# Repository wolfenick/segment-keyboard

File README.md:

# SEGMENT Keyboard

SEGMENT is a 60% form factor keyboard featuring only through-hole components, drawing design inspiration from PCB's of the 1980s. This project is still in the early stages of design and testing.

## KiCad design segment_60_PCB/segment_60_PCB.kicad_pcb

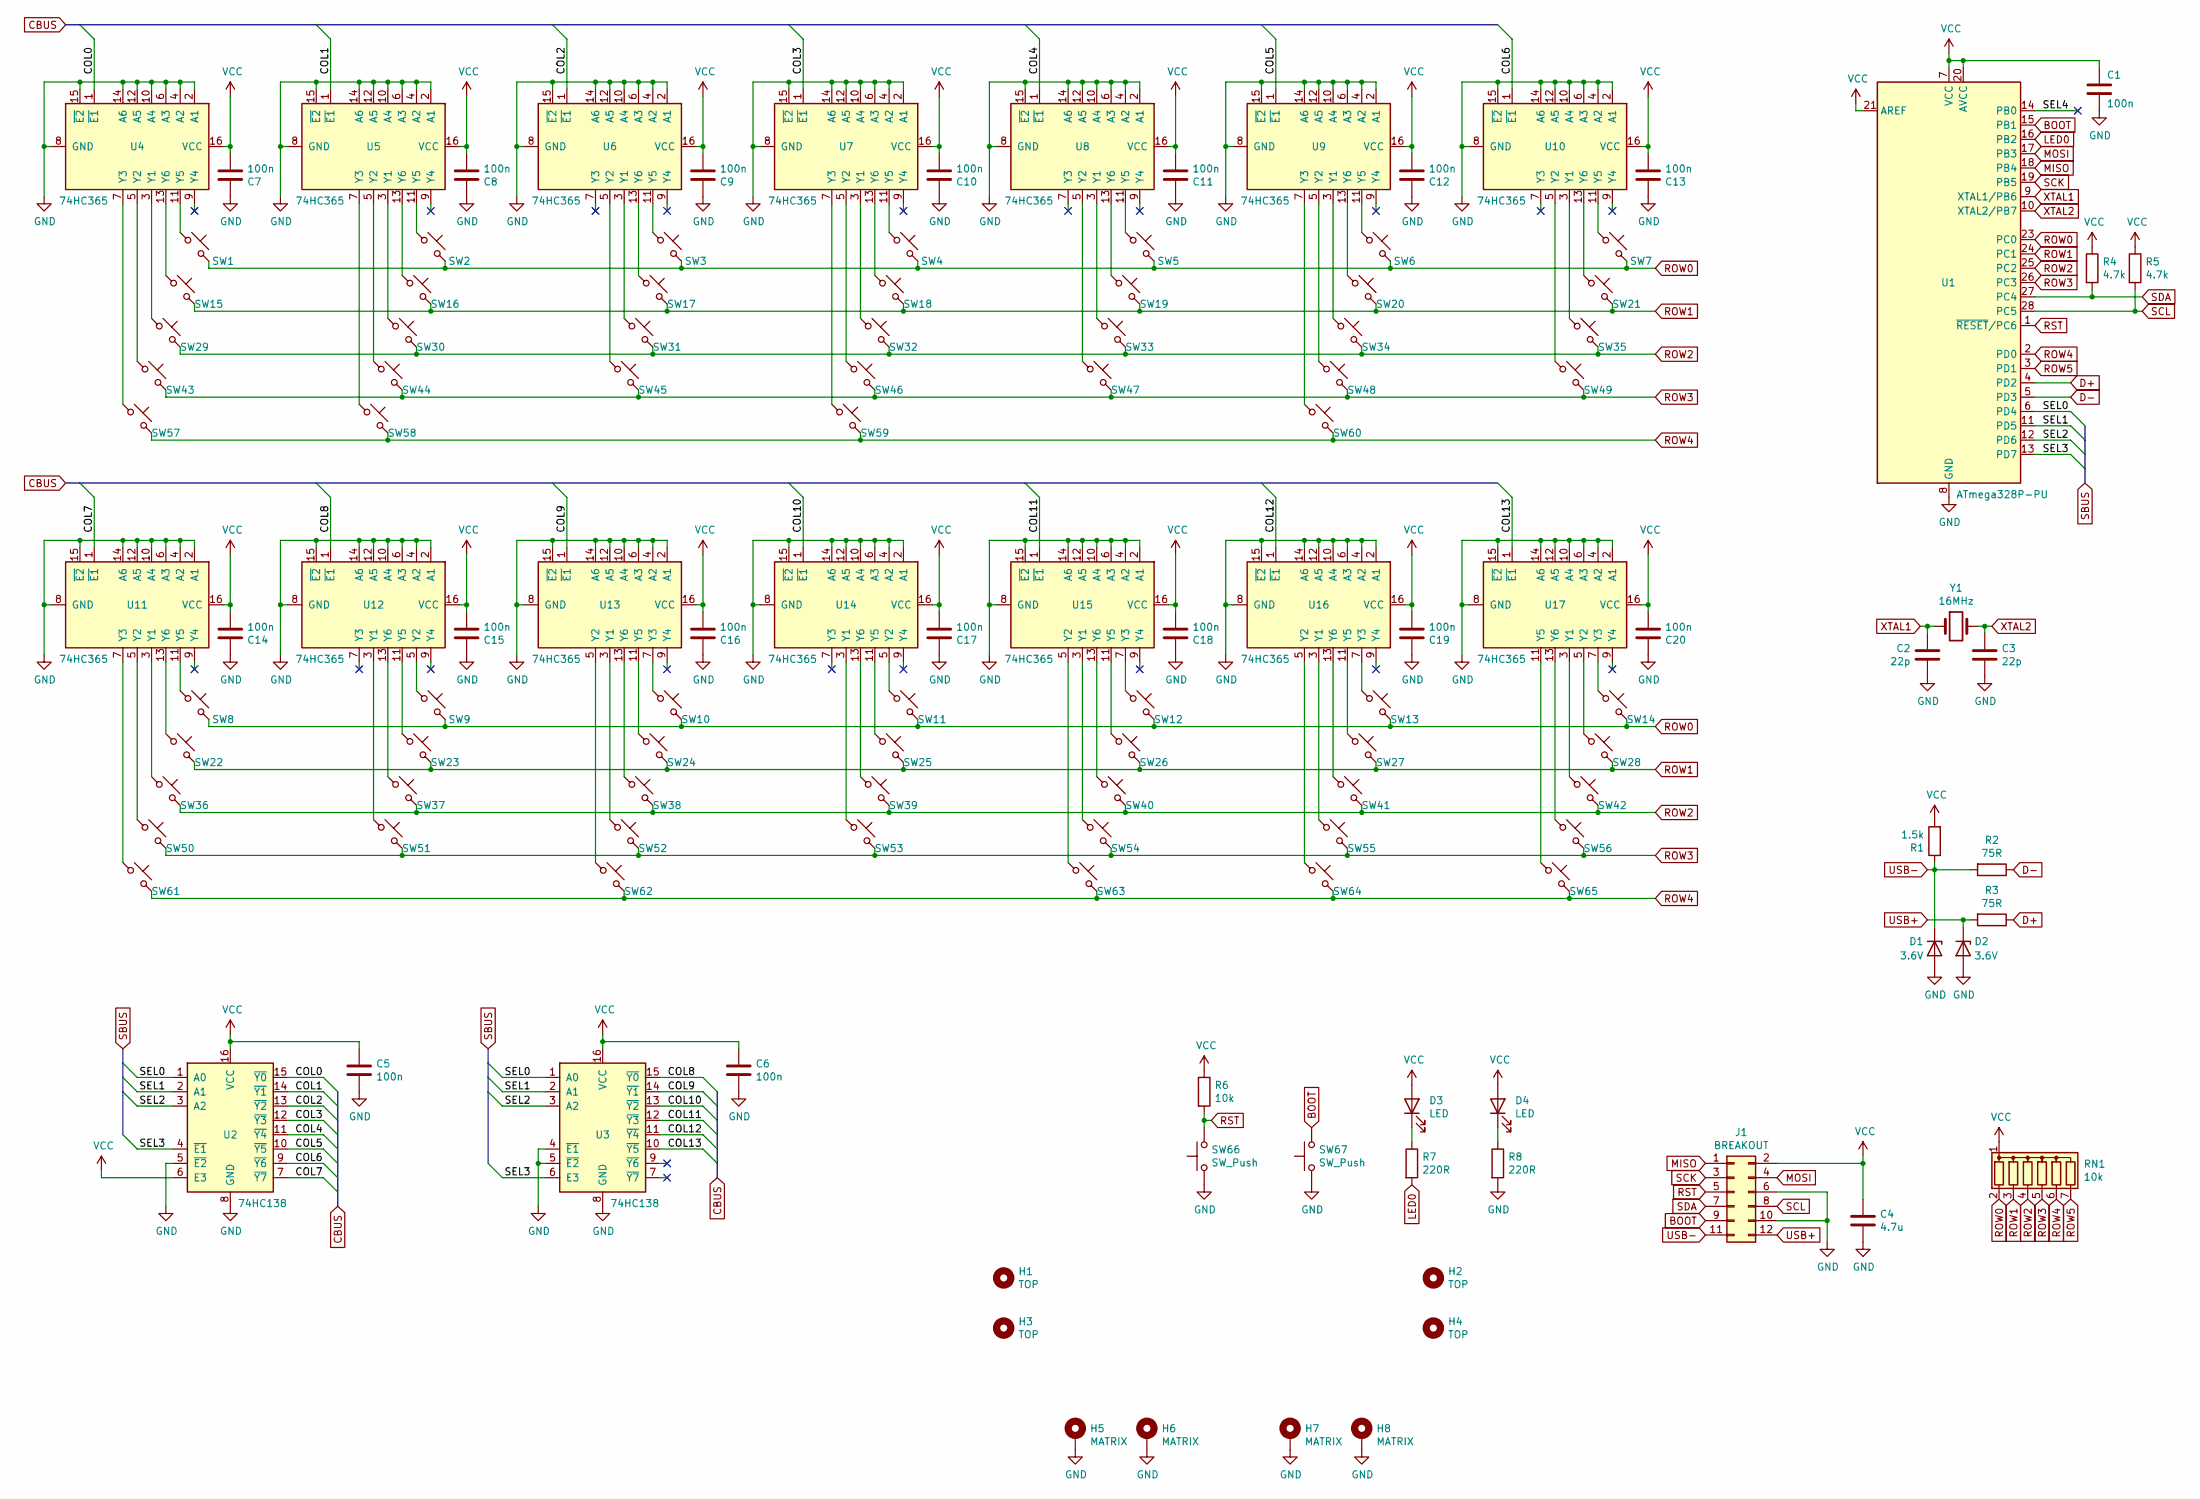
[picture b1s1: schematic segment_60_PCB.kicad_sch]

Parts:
C1: 100n; C_Axial_L3.8mm_D2.6mm_P10.16mm_Horizontal
C2, C3: 22p; C_Disc_D3.0mm_W1.6mm_P2.50mm
C4: 4.7u; CP_Axial_L11.0mm_D5.0mm_P18.00mm_Horizontal
C5, C6, C7, C8, C9, C10, C11, C12, C13, C14, C15, C16, C17, C18, C19, C20: 100n; C_Axial_L3.8mm_D2.6mm_P7.62mm_Horizontal
D1, D2: 3.6V; D_DO-35_SOD27_P10.16mm_Horizontal
D3, D4: LED; LED_D5.0mm
H1, H2, H3, H4: TOP; MountingHole_3.2mm_M3
H5, H6, H7, H8: MATRIX; MountingHole_3.2mm_M3_Pad
J1: BREAKOUT; IDC-Header_2x06_P2.54mm_Vertical
R1: 1.5k; R_Axial_DIN0207_L6.3mm_D2.5mm_P10.16mm_Horizontal
R2, R3: 75R; R_Axial_DIN0207_L6.3mm_D2.5mm_P10.16mm_Horizontal
R4, R5: 4.7k; R_Axial_DIN0207_L6.3mm_D2.5mm_P10.16mm_Horizontal
R6: 10k; R_Axial_DIN0207_L6.3mm_D2.5mm_P10.16mm_Horizontal
R7, R8: 220R; R_Axial_DIN0207_L6.3mm_D2.5mm_P10.16mm_Horizontal
RN1: 10k; R_Array_SIP7
SW1, SW2, SW3, SW4, SW5, SW6, SW7, SW8, SW9, SW10, SW11, SW12, SW13, SW16, SW17, SW18, SW19, SW20, SW21, SW22, SW23, SW24, SW25, SW26, SW27, SW28, SW30, SW31, SW32, SW33, SW34, SW35, SW36, SW37, SW38, SW39, SW40, SW44, SW45, SW46, SW47, SW48, SW49, SW50, SW51, SW52, SW53, SW54, SW56, SW58, SW64: SW_Push_45deg; Segment_MX_1.00u_PCB
SW14: SW_Push_45deg; Segment_MX_1.00u_2.00u_PCB
SW15, SW57, SW59, SW63, SW65: SW_Push_45deg; Segment_MX_1.50u_PCB
SW29: SW_Push_45deg; Segment_MX_1.25u_1.75u_PCB
SW41: SW_Push_45deg; Segment_MX_1.00u_2.25u_PCB
SW42: SW_Push_45deg; Segment_MX_1.50u_ISO_PCB
SW43: SW_Push_45deg; Segment_MX_1.25u_2.25u_PCB
SW55: SW_Push_45deg; Segment_MX_1.75u_2.75u_PCB
SW60, SW62: SW_Push_45deg; Segment_MX_2.75u_PCB
SW61: SW_Push_45deg; Segment_MX_7.00u_PCB
SW66, SW67: SW_Push; SW_PUSH_6mm
U1: ATmega328P-PU; DIP-28_W7.62mm
U2, U3: 74HC138; DIP-16_W7.62mm
U4, U5, U6, U7, U8, U9, U10, U11, U12, U13, U14, U15, U16, U17: 74HC365; DIP-16_W7.62mm
Y1: 16MHz; Crystal_HC49-4H_Vertical

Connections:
/COL0: U2.15 (~Y0), U4.1 (~E1)
/COL1: U2.14 (~Y1), U5.1 (~E1)
/COL2: U2.13 (~Y2), U6.1 (~E1)
/COL3: U2.12 (~Y3), U7.1 (~E1)
/COL4: U2.11 (~Y4), U8.1 (~E1)
/COL5: U2.10 (~Y5), U9.1 (~E1)
/COL6: U2.9 (~Y6), U10.1 (~E1)
/COL7: U2.7 (~Y7), U11.1 (~E1)
/COL8: U3.15 (~Y0), U12.1 (~E1)
/COL9: U3.14 (~Y1), U13.1 (~E1)
/COL10: U3.13 (~Y2), U14.1 (~E1)
/COL11: U3.12 (~Y3), U15.1 (~E1)
/COL12: U3.11 (~Y4), U16.1 (~E1)
/COL13: U3.10 (~Y5), U17.1 (~E1)
/SEL0: U1.6 (PD4), U2.1 (A0), U3.1 (A0)
/SEL1: U1.11 (PD5), U2.2 (A1), U3.2 (A1)
/SEL2: U1.12 (PD6), U2.3 (A2), U3.3 (A2)
/SEL3: U1.13 (PD7), U2.4 (~E1), U3.6 (E3)
/SEL4: U1.14 (PB0)
BOOT: J1.9, SW67.2, U1.15 (PB1)
D+: R3.1, U1.4 (PD2)
D-: R2.1, U1.5 (PD3)
GND: C1.2, C2.1, C3.2, C4.2, C5.2, C6.2, C7.1, C8.1, C9.1, C10.1, C11.1, C12.1, C13.1, C14.1, C15.1, C16.1, C17.1, C18.1, C19.1, C20.1, D1.2 (A), D2.2 (A), H5.1, H6.1, H7.1, H8.1, J1.6, J1.10, R8.2, SW66.1, SW67.1, U1.8 (GND), U1.22 (GND), U2.5 (~E2), U2.8 (GND), U3.4 (~E1), U3.5 (~E2), U3.8 (GND), U4.2 (A1), U4.4 (A2), U4.6 (A3), U4.8 (GND), U4.10 (A4), U4.12 (A5), U4.14 (A6), U4.15 (~E2), U5.2 (A1), U5.4 (A2), U5.6 (A3), U5.8 (GND), U5.10 (A4), U5.12 (A5), U5.14 (A6), U5.15 (~E2), U6.2 (A1), U6.4 (A2), U6.6 (A3), U6.8 (GND), U6.10 (A4), U6.12 (A5), U6.14 (A6), U6.15 (~E2), U7.2 (A1), U7.4 (A2), U7.6 (A3), U7.8 (GND), U7.10 (A4), U7.12 (A5), U7.14 (A6), U7.15 (~E2), U8.2 (A1), U8.4 (A2), U8.6 (A3), U8.8 (GND), U8.10 (A4), U8.12 (A5), U8.14 (A6), U8.15 (~E2), U9.2 (A1), U9.4 (A2), U9.6 (A3), U9.8 (GND), U9.10 (A4), U9.12 (A5), U9.14 (A6), U9.15 (~E2), U10.2 (A1), U10.4 (A2), U10.6 (A3), U10.8 (GND), U10.10 (A4), U10.12 (A5), U10.14 (A6), U10.15 (~E2), U11.2 (A1), U11.4 (A2), U11.6 (A3), U11.8 (GND), U11.10 (A4), U11.12 (A5), U11.14 (A6), U11.15 (~E2), U12.2 (A1), U12.4 (A2), U12.6 (A3), U12.8 (GND), U12.10 (A4), U12.12 (A5), U12.14 (A6), U12.15 (~E2), U13.2 (A1), U13.4 (A2), U13.6 (A3), U13.8 (GND), U13.10 (A4), U13.12 (A5), U13.14 (A6), U13.15 (~E2), U14.2 (A1), U14.4 (A2), U14.6 (A3), U14.8 (GND), U14.10 (A4), U14.12 (A5), U14.14 (A6), U14.15 (~E2), U15.2 (A1), U15.4 (A2), U15.6 (A3), U15.8 (GND), U15.10 (A4), U15.12 (A5), U15.14 (A6), U15.15 (~E2), U16.2 (A1), U16.4 (A2), U16.6 (A3), U16.8 (GND), U16.10 (A4), U16.12 (A5), U16.14 (A6), U16.15 (~E2), U17.2 (A1), U17.4 (A2), U17.6 (A3), U17.8 (GND), U17.10 (A4), U17.12 (A5), U17.14 (A6), U17.15 (~E2); also elsewhere on the board
LED0: R7.2, U1.16 (PB2)
MISO: J1.1, U1.18 (PB4)
MOSI: J1.4, U1.17 (PB3)
unnamed: D3.1 (K), R7.1
unnamed: D4.1 (K), R8.1
unnamed: SW1.1, U4.11 (Y5)
unnamed: SW2.1, U5.11 (Y5)
unnamed: SW3.1, U6.11 (Y5)
unnamed: SW4.1, U7.11 (Y5)
unnamed: SW5.1, U8.11 (Y5)
unnamed: SW6.1, U9.11 (Y5)
unnamed: SW7.1, U10.11 (Y5)
unnamed: SW8.1, U11.11 (Y5)
unnamed: SW9.1, U12.5 (Y2)
unnamed: SW10.1, U13.7 (Y3)
unnamed: SW11.1, U14.5 (Y2)
unnamed: SW12.1, U15.7 (Y3)
unnamed: SW13.1, U16.7 (Y3)
unnamed: SW14.1, U17.7 (Y3)
unnamed: SW15.1, U4.13 (Y6)
unnamed: SW16.1, U5.13 (Y6)
unnamed: SW17.1, U6.13 (Y6)
unnamed: SW18.1, U7.13 (Y6)
unnamed: SW19.1, U8.13 (Y6)
unnamed: SW20.1, U9.13 (Y6)
unnamed: SW21.1, U10.13 (Y6)
unnamed: SW22.1, U11.13 (Y6)
unnamed: SW23.1, U12.11 (Y5)
unnamed: SW24.1, U13.11 (Y5)
unnamed: SW25.1, U14.11 (Y5)
unnamed: SW26.1, U15.11 (Y5)
unnamed: SW27.1, U16.11 (Y5)
unnamed: SW28.1, U17.5 (Y2)
unnamed: SW29.1, U4.3 (Y1)
unnamed: SW30.1, U5.3 (Y1)
unnamed: SW31.1, U6.3 (Y1)
unnamed: SW32.1, U7.3 (Y1)
unnamed: SW33.1, U8.3 (Y1)
unnamed: SW34.1, U9.3 (Y1)
unnamed: SW35.1, U10.3 (Y1)
unnamed: SW36.1, U11.3 (Y1)
unnamed: SW37.1, U12.13 (Y6)
unnamed: SW38.1, U13.13 (Y6)
unnamed: SW39.1, U14.13 (Y6)
unnamed: SW40.1, U15.13 (Y6)
unnamed: SW41.1, U16.13 (Y6)
unnamed: SW42.1, U17.3 (Y1)
unnamed: SW43.1, U4.5 (Y2)
unnamed: SW44.1, U5.5 (Y2)
unnamed: SW45.1, U6.5 (Y2)
unnamed: SW46.1, U7.5 (Y2)
unnamed: SW47.1, U8.5 (Y2)
unnamed: SW48.1, U9.5 (Y2)
unnamed: SW49.1, U10.5 (Y2)
unnamed: SW50.1, U11.5 (Y2)
unnamed: SW51.1, U12.3 (Y1)
unnamed: SW52.1, U13.3 (Y1)
unnamed: SW53.1, U14.3 (Y1)
unnamed: SW54.1, U15.3 (Y1)
unnamed: SW55.1, U16.3 (Y1)
unnamed: SW56.1, U17.13 (Y6)
unnamed: SW57.1, U4.7 (Y3)
unnamed: SW58.1, U5.7 (Y3)
unnamed: SW59.1, U7.7 (Y3)
unnamed: SW60.1, U9.7 (Y3)
unnamed: SW61.1, U11.7 (Y3)
unnamed: SW62.1, U13.5 (Y2)
unnamed: SW63.1, U15.5 (Y2)
unnamed: SW64.1, U16.5 (Y2)
unnamed: SW65.1, U17.11 (Y5)
ROW0: RN1.2 (R1), SW1.2, SW2.2, SW3.2, SW4.2, SW5.2, SW6.2, SW7.2, SW8.2, SW9.2, SW10.2, SW11.2, SW12.2, SW13.2, SW14.2, U1.23 (PC0)
ROW1: RN1.3 (R2), SW15.2, SW16.2, SW17.2, SW18.2, SW19.2, SW20.2, SW21.2, SW22.2, SW23.2, SW24.2, SW25.2, SW26.2, SW27.2, SW28.2, U1.24 (PC1)
ROW2: RN1.4 (R3), SW29.2, SW30.2, SW31.2, SW32.2, SW33.2, SW34.2, SW35.2, SW36.2, SW37.2, SW38.2, SW39.2, SW40.2, SW41.2, SW42.2, U1.25 (PC2)
ROW3: RN1.5 (R4), SW43.2, SW44.2, SW45.2, SW46.2, SW47.2, SW48.2, SW49.2, SW50.2, SW51.2, SW52.2, SW53.2, SW54.2, SW55.2, SW56.2, U1.26 (PC3)
ROW4: RN1.6 (R5), SW57.2, SW58.2, SW59.2, SW60.2, SW61.2, SW62.2, SW63.2, SW64.2, SW65.2, U1.2 (PD0)
ROW5: RN1.7 (R6), U1.3 (PD1)
RST: J1.5, R6.2, SW66.2, U1.1 (~RESET/PC6)
SCK: J1.3, U1.19 (PB5)
SCL: J1.8, R5.2, U1.28 (PC5)
SDA: J1.7, R4.2, U1.27 (PC4)
USB+: D2.1 (K), J1.12, R3.2
USB-: D1.1 (K), J1.11, R1.1, R2.2
VCC: C1.1, C4.1, C5.1, C6.1, C7.2, C8.2, C9.2, C10.2, C11.2, C12.2, C13.2, C14.2, C15.2, C16.2, C17.2, C18.2, C19.2, C20.2, D3.2 (A), D4.2 (A), J1.2, R1.2, R4.1, R5.1, R6.1, RN1.1 (common), U1.7 (VCC), U1.20 (AVCC), U1.21 (AREF), U2.6 (E3), U2.16 (VCC), U3.16 (VCC), U4.16 (VCC), U5.16 (VCC), U6.16 (VCC), U7.16 (VCC), U8.16 (VCC), U9.16 (VCC), U10.16 (VCC), U11.16 (VCC), U12.16 (VCC), U13.16 (VCC), U14.16 (VCC), U15.16 (VCC), U16.16 (VCC), U17.16 (VCC)
XTAL1: C2.2, U1.9 (XTAL1/PB6), Y1.1
XTAL2: C3.1, U1.10 (XTAL2/PB7), Y1.2

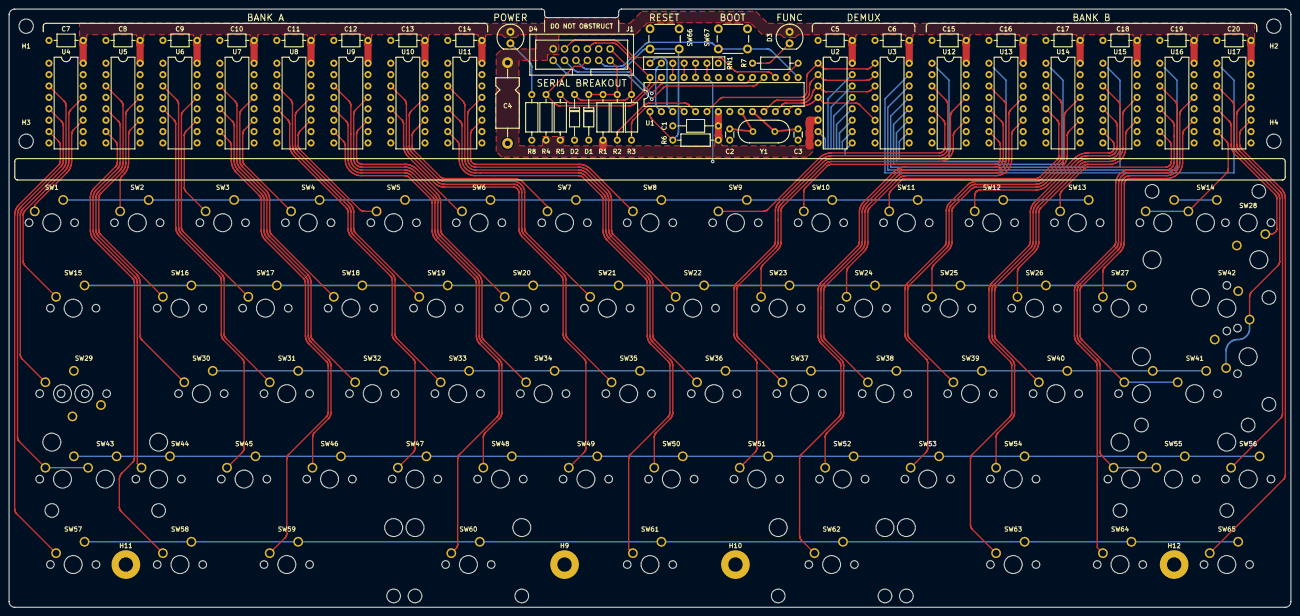
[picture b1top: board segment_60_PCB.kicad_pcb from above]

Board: 2 copper layers, 285.8 x 133.4 mm, 127 parts (0 on the bottom side), 107 nets.

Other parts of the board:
H9, H10, H11, H12: MATRIX; MountingHole_3.2mm_M3_Pad

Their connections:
GND: H9.1, H10.1, H11.1, H12.1; also elsewhere on the board

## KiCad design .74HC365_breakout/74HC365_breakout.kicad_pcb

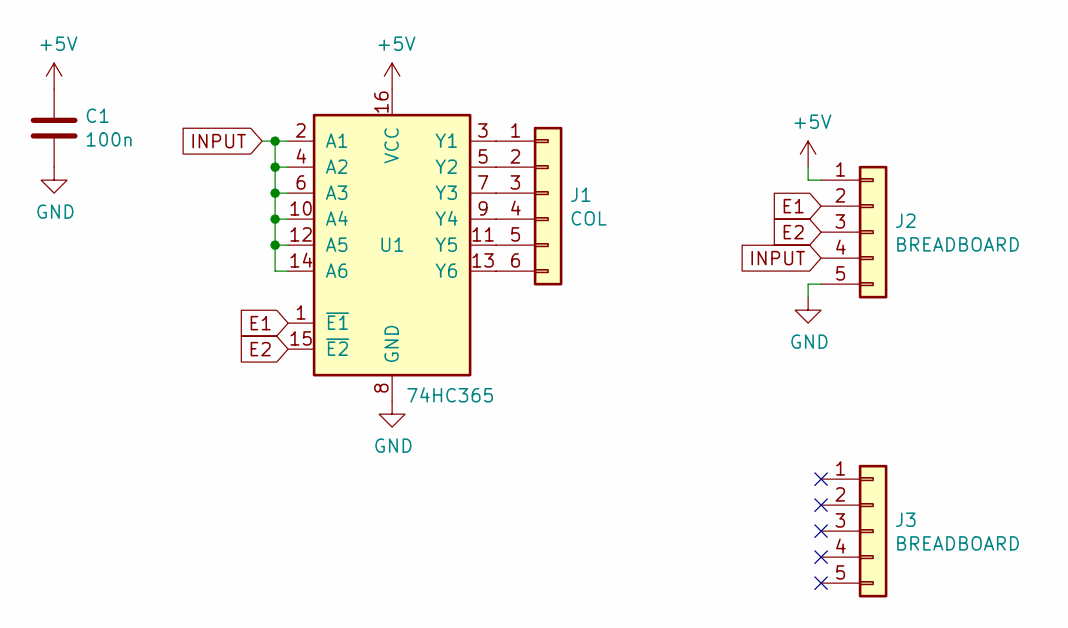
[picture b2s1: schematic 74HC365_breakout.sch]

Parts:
C1: 100n; C_Disc_D3.0mm_W1.6mm_P2.50mm
J1: COL; PinHeader_1x06_P2.54mm_Vertical
J2, J3: BREADBOARD; PinHeader_1x05_P2.54mm_Vertical
U1: 74HC365; DIP-16_W7.62mm

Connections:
+5V: C1.1, J2.1, U1.16 (VCC)
E1: J2.2, U1.1 (~E1)
E2: J2.3, U1.15 (~E2)
GND: C1.2, J2.5, U1.8 (GND)
INPUT: J2.4, U1.2 (A1), U1.4 (A2), U1.6 (A3), U1.10 (A4), U1.12 (A5), U1.14 (A6)
unnamed: J1.1, U1.3 (Y1)
unnamed: J1.2, U1.5 (Y2)
unnamed: J1.3, U1.7 (Y3)
unnamed: J1.4, U1.9 (Y4)
unnamed: J1.5, U1.11 (Y5)
unnamed: J1.6, U1.13 (Y6)

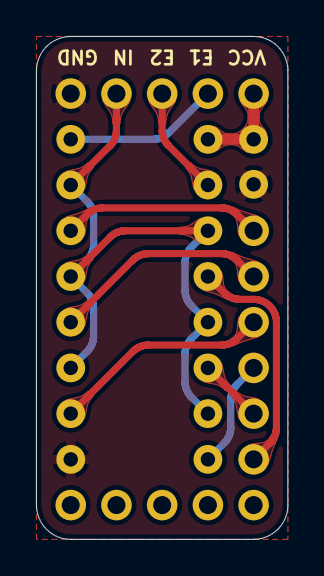
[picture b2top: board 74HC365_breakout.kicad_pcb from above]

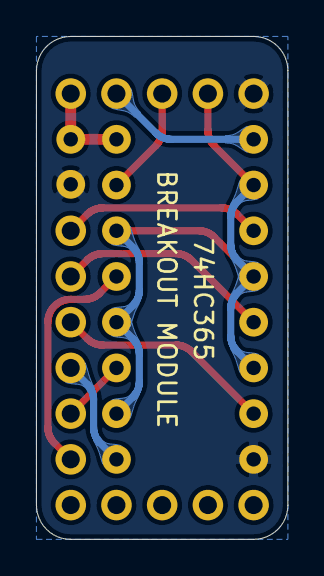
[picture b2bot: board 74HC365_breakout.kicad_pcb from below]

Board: 2 copper layers, 14.0 x 27.9 mm, 5 parts (2 on the bottom side), 11 nets.

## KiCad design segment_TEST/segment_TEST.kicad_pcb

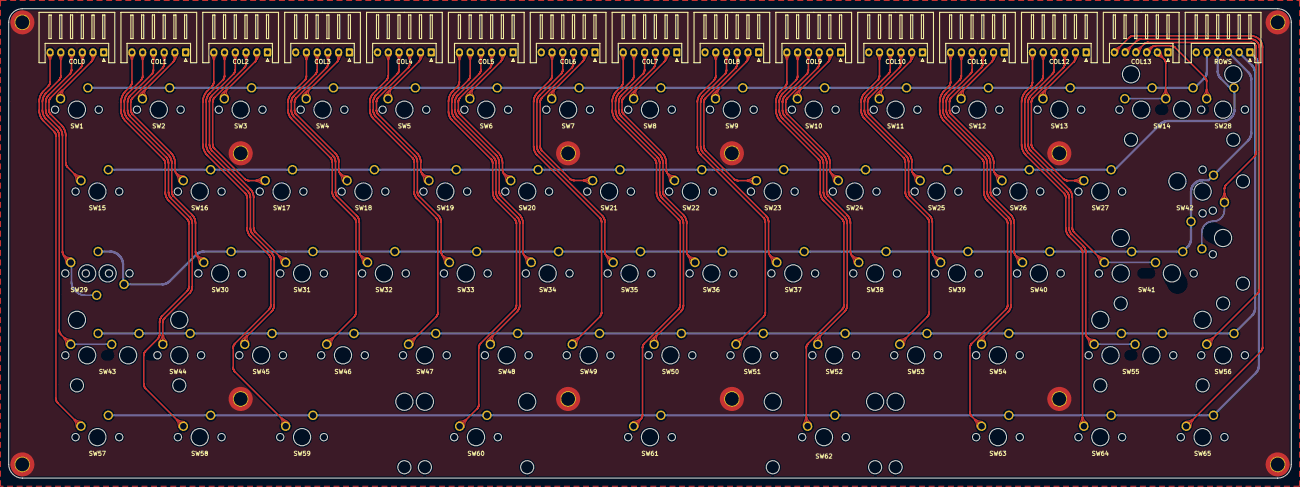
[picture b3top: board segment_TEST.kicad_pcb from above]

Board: 2 copper layers, 298.4 x 109.2 mm, 92 parts (0 on the bottom side), 71 nets.

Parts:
COL0: COL0; JST_XH_S6B-XH-A_1x06_P2.50mm_Horizontal
COL1: COL1; JST_XH_S6B-XH-A_1x06_P2.50mm_Horizontal
COL2: COL2; JST_XH_S6B-XH-A_1x06_P2.50mm_Horizontal
COL3: COL3; JST_XH_S6B-XH-A_1x06_P2.50mm_Horizontal
COL4: COL4; JST_XH_S6B-XH-A_1x06_P2.50mm_Horizontal
COL5: COL5; JST_XH_S6B-XH-A_1x06_P2.50mm_Horizontal
COL6: COL6; JST_XH_S6B-XH-A_1x06_P2.50mm_Horizontal
COL7: COL7; JST_XH_S6B-XH-A_1x06_P2.50mm_Horizontal
COL8: COL8; JST_XH_S6B-XH-A_1x06_P2.50mm_Horizontal
COL9: COL9; JST_XH_S6B-XH-A_1x06_P2.50mm_Horizontal
COL10: COL10; JST_XH_S6B-XH-A_1x06_P2.50mm_Horizontal
COL11: COL11; JST_XH_S6B-XH-A_1x06_P2.50mm_Horizontal
COL12: COL12; JST_XH_S6B-XH-A_1x06_P2.50mm_Horizontal
COL13: COL13; JST_XH_S6B-XH-A_1x06_P2.50mm_Horizontal
H1, H2, H3, H4, H5, H6, H7, H8, H9, H10, H11, H12: MountingHole_Pad; MountingHole_3.2mm_M3_DIN965_Pad_TopBottom
ROWS: ROWS; JST_XH_S6B-XH-A_1x06_P2.50mm_Horizontal
SW1, SW2, SW3, SW4, SW5, SW6, SW7, SW8, SW9, SW10, SW11, SW12, SW13, SW16, SW17, SW18, SW19, SW20, SW21, SW22, SW23, SW24, SW25, SW26, SW27, SW28, SW30, SW31, SW32, SW33, SW34, SW35, SW36, SW37, SW38, SW39, SW40, SW44, SW45, SW46, SW47, SW48, SW49, SW50, SW51, SW52, SW53, SW54, SW56, SW58, SW64: SW_Push_45deg; Segment_MX_1.00u_PCB
SW14: SW_Push_45deg; Segment_MX_1.00u_2.00u_PCB
SW15, SW57, SW59, SW63, SW65: SW_Push_45deg; Segment_MX_1.50u_PCB
SW29: SW_Push_45deg; Segment_MX_1.25u_1.75u_PCB
SW41: SW_Push_45deg; Segment_MX_1.00u_2.25u_PCB
SW42: SW_Push_45deg; Segment_MX_1.50u_ISO_PCB
SW43: SW_Push_45deg; Segment_MX_1.25u_2.25u_PCB
SW55: SW_Push_45deg; Segment_MX_1.75u_2.75u_PCB
SW60, SW62: SW_Push_45deg; Segment_MX_2.75u_PCB
SW61: SW_Push_45deg; Segment_MX_7.00u_PCB

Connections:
GND: H1.1, H2.1, H3.1, H4.1, H5.1, H6.1, H7.1, H8.1, H9.1, H10.1, H11.1, H12.1
unnamed: COL0.2, SW1.1
unnamed: COL0.3, SW15.1
unnamed: COL0.4, SW29.1
unnamed: COL0.5, SW43.1
unnamed: COL0.6, SW57.1
unnamed: COL1.2, SW2.1
unnamed: COL1.3, SW16.1
unnamed: COL1.4, SW30.1
unnamed: COL1.5, SW44.1
unnamed: COL1.6, SW58.1
unnamed: COL2.2, SW3.1
unnamed: COL2.3, SW17.1
unnamed: COL2.4, SW31.1
unnamed: COL2.5, SW45.1
unnamed: COL2.6, SW59.1
unnamed: COL3.2, SW4.1
unnamed: COL3.3, SW18.1
unnamed: COL3.4, SW32.1
unnamed: COL3.5, SW46.1
unnamed: COL4.2, SW5.1
unnamed: COL4.3, SW19.1
unnamed: COL4.4, SW33.1
unnamed: COL4.5, SW47.1
unnamed: COL5.2, SW6.1
unnamed: COL5.3, SW20.1
unnamed: COL5.4, SW34.1
unnamed: COL5.5, SW48.1
unnamed: COL5.6, SW60.1
unnamed: COL6.2, SW7.1
unnamed: COL6.3, SW21.1
unnamed: COL6.4, SW35.1
unnamed: COL6.5, SW49.1
unnamed: COL7.2, SW8.1
unnamed: COL7.3, SW22.1
unnamed: COL7.4, SW36.1
unnamed: COL7.5, SW50.1
unnamed: COL7.6, SW61.1
unnamed: COL8.2, SW9.1
unnamed: COL8.3, SW23.1
unnamed: COL8.4, SW37.1
unnamed: COL8.5, SW51.1
unnamed: COL9.2, SW10.1
unnamed: COL9.3, SW24.1
unnamed: COL9.4, SW38.1
unnamed: COL9.5, SW52.1
unnamed: COL9.6, SW62.1
unnamed: COL10.2, SW11.1
unnamed: COL10.3, SW25.1
unnamed: COL10.4, SW39.1
unnamed: COL10.5, SW53.1
unnamed: COL11.2, SW12.1
unnamed: COL11.3, SW26.1
unnamed: COL11.4, SW40.1
unnamed: COL11.5, SW54.1
unnamed: COL11.6, SW63.1
unnamed: COL12.2, SW13.1
unnamed: COL12.3, SW27.1
unnamed: COL12.4, SW41.1
unnamed: COL12.5, SW55.1
unnamed: COL12.6, SW64.1
unnamed: COL13.2, SW14.1
unnamed: COL13.3, SW28.1
unnamed: COL13.4, SW42.1
unnamed: COL13.5, SW56.1
unnamed: COL13.6, SW65.1
ROW0: ROWS.1, SW57.2, SW58.2, SW59.2, SW60.2, SW61.2, SW62.2, SW63.2, SW64.2, SW65.2
ROW1: ROWS.2, SW43.2, SW44.2, SW45.2, SW46.2, SW47.2, SW48.2, SW49.2, SW50.2, SW51.2, SW52.2, SW53.2, SW54.2, SW55.2, SW56.2
ROW2: ROWS.3, SW29.2, SW30.2, SW31.2, SW32.2, SW33.2, SW34.2, SW35.2, SW36.2, SW37.2, SW38.2, SW39.2, SW40.2, SW41.2, SW42.2
ROW3: ROWS.4, SW15.2, SW16.2, SW17.2, SW18.2, SW19.2, SW20.2, SW21.2, SW22.2, SW23.2, SW24.2, SW25.2, SW26.2, SW27.2, SW28.2
ROW4: ROWS.5, SW1.2, SW2.2, SW3.2, SW4.2, SW5.2, SW6.2, SW7.2, SW8.2, SW9.2, SW10.2, SW11.2, SW12.2, SW13.2, SW14.2

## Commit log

2020-08-04 Initial commit with local work
2020-08-04 Added README.md
2020-08-04 Added license
2020-08-05 Updated schematic and library names
2020-08-05 Updated switch matrix
2020-11-13 added .gitignore
2020-11-18 Fixed USB config; introduced '365 buffers in place of diodes
2020-11-21 replaced USB-C with DE-9.
2020-12-05 Added ATmega328P
2021-03-02 Started mock keyboard
2021-03-02 Completed test board layout; implementing option footprints
2021-03-05 Layout mostly complete for test board
2021-03-05 Added JST-XH connectors to test board
2021-03-06 Added mounting holes to test board
2021-03-10 Finished test board design
2021-03-11 Minor tweak to test board
2021-03-25 Updated test board
2021-06-14 Added test board dimensions
2021-11-20 Updated KiCAD project names in preparation for new keyboards; minor changes to SEGMENT-60 schematic.
2021-11-21 Majorly updated SEGMENT 60 schematic to display a more representative matrix arrangement; annotated and began footprint assignment.
2021-11-21 Updated keyswitch footprints to correct sizes.
2021-11-22 Started SEGMENT 60 layout
2021-11-22 Continued organizing footprints and minor layout changes to control hardware.
2021-11-22 Removed resources folder.
2021-11-22 Cleaned up repository; removed resources folder, renamed layouts, removed some outdated production files.
2021-11-23 Added remaining footprints, changed library paths to be relative.
2021-11-23 Tweaked layout.
2021-11-24 Updated layout; changed row pullup resistors to a single resistor network
2021-11-24 added border, changed J1 footprint and model
2021-11-25 Updated switch footprints to include 3D models
2021-11-28 Added power pours for VCC
2021-11-28 Routed some more logic lines; continued adding and chaning VCC pours
2021-11-30 Routed first 8 columns of switches
2021-12-01 Updated symbols for 74HC365; routed all buffer to switch connections
2021-12-02 Attempted routing plan for column select traces
2022-01-16 Finished design and layout of SEGMENT-60 main PCB
2022-01-16 Finished SEGMENT-60 PCB and produced production files
2022-01-17 Updated SEGMENT-60 fill zone
2022-01-19 Updated SEGMENT-60 gerber files
2022-02-18 Started overhauling footprint silkscreens
2022-02-23 Updated all footprints; performing new layout
2022-03-21 Added QMK keyboard folder locally
2022-05-21 Finished silkscreen revisions.
